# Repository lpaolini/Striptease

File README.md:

# Striptease

Sexy, audio-responsive effects on LED strips.

For [Teensy 4](https://www.pjrc.com/store/teensy40.html) with [Audio Adapter Board](https://www.pjrc.com/store/teensy3_audio.html), by [PJRC](https://www.pjrc.com).

## Quick demo

Shooting video of LEDs is very tricky. Getting the right exposure, focus and colors is not easy at all.
I did my best, but the live effect from my couch is simply not comparable with what you get on video.
I think the main reason is frame rate. This video has been shot at 60 fps, but the real animation runs at about __170 fps__...

[Effect showcase](https://youtu.be/ZliKL7l32wE) (version 3, April 2021)

# Intro

I **love** lights, especially LED lights.

The main goals of this library are:

- to simplify the development of visual effects to be rendered on LED strips, by providing useful abstractions and helpers
- to provide runtime support for rendering simultaneous effects on multiple strips, controlling the transitions and adjusting parameters in real time

# Credits

This work has been inspired by some very cool projects published on the [Cine-Lights](https://www.youtube.com/channel/UCOG6Bi2kvpDa1c8gHWZI5CQ) YouTube channel.
Some of the effects still keep the same name as originally given by the author, even though they have been reimplemented from scratch and might look very different.

Note: at some point, the author decided to go closed-source, distributing compiled (.hex) files only.

# Hardware

## Teensy

This library is designed around the awesome Teensy 4 Development Board, available as [Teensy 4.0](https://www.pjrc.com/store/teensy40.html) or [Teensy 4.1](https://www.pjrc.com/store/teensy41.html), which has been chosen for a number of reasons:

- It's an extremely capable Arduino-compatible board, running an ARM Cortex-M7 at 600 MHz with a floating point math unit, 64 & 32 bits;
- It can be combined with the [Audio Adapter Board](https://www.pjrc.com/store/teensy3_audio.html) for audio I/O and processing;
- It comes with a large set of libraries including two great ones by Paul Stoffregen (Audio and WS2812Serial), described below;
- It's relatively cheap, compared to what it offers.

## Audio Board

The Audio Adapter Board **rev. D** (specific for Teensy 4.x) provides CD-quality stereo ADC/DAC and hardware processing of audio signals.
An optional microphone can be soldered to the board to provide software-switchable mono microphone input, in addition to stereo line input.

Teensy 4.0 provides five serial ports suitable for non-blocking LED driving, while Teensy 4.1 provides a total of eight.
However, when using the Audio Adapter Board, Serial2 and Serial5 are unavailable, leaving us with three channels for Teensy 4.0 and six for Teensy 4.1.

## Level shifter

Teensy 4 runs at 3.3v and all I/O ports operate exclusively at this voltage, thus a level shifter (74HCT245) is required to reliably drive WS2812B LEDs with 5v signals.

## Main board

I've designed a couple of custom PCBs, available in the *hardware* directory: one for Teensy 4.0, the other one for Teensy 4.1, housing connectors (power, IR receiver and LEDs), the DIL socket for the 74HCT245 IC, and a pair of stripline sockets for the Teensy, plus a few passive components. The Audio Adapter Board is sandwiched between the main board and the Teensy using long-terminal stripline connectors soldered to the Audio Adapter Board.

PCBs have been designed using [EAGLE PCB](https://www.autodesk.com/products/eagle) and fabricated by [JLCPCB](https://jlcpcb.com/).

### Main board connectors - Teensy 4.0 version (3 channels)

- POWER: Power (GND, +5v)
- IR-RECV: IR receiver (GND, Data, +3.3v)
- LED1-4: LEDs (CH1, CH2, CH3, CH3)

Note: CH3 is repeated because there are only three independent outputs

### Main board connectors - Teensy 4.1 version (6 channels)

- POWER: Power (GND, +5v)
- IR-RECV: IR receiver (GND, Data, +3.3v)
- PROGR: Program button
- LED1-4: LEDs (CH1, CH2, CH3, CH4)
- LED5-8: LEDs (CH5, CH6, CH6, CH6)

Note: CH6 is repeated because there are only six independent outputs

## WS2812B LED strips

For my projects I prefer high density WS2812B LED strips (144 LED/m) with semi-transparent diffuser, because they look amazing at short distance.
I'm providing photos of the diffuser on top of a printed page, to give you an idea of the transparency.

### Update rate (FPS)

Strips can be any length and they don't need to be matched.
However, being channels driven in parallel, the global update rate is the update rate of the longest strip.
Update rate can be calculated multiplying the time required for transmitting RGB data for a single WS2812B LED (30us) by the number of the LEDs in the strip.
With 6 channels available, up to 3324 LEDs can be driven at 60fps, or up to 1662 at 120fps.
In my home application (about 800 LEDs), the longest strip has 192 LEDs, which translates to about 170fps.

### Powering LEDs

Please be aware that the power rails on the strips have a non-negligible resistance, which would inevitably cause a voltage drop over distance.
The higher the current, the higher the voltage drop (ohm's law).
Total current is the sum of the current flowing through individual LEDs, which in turn depends on the RGB values.
So, depending on the instantaneous state of the LEDs in the strip, the voltage drop could be enough to cause malfunctioning.
To overcome this problem, you might need to *inject* power also at the end of the strip and, if it's very long, every n LEDs (n to be determined).

Personally, I never had to do this, even when driving 240 LEDs at full brightness, but copper thickness of the power rails might differ from one producer to another.

## Power supply

I suggest using excellent quality power supplies. A faulty one can easily destroy your hardware and can even become a threat for your life!

One of my favorite brands is [Traco Power](https://www.tracopower.com/).

## Connectors

For connecting strips to the controller I use professional [Neutrik](https://www.neutrik.com) speakON connectors: [NL4FX](https://www.neutrik.com/en/product/nl4fx) on the cable and [NL4MP](https://www.neutrik.com/en/product/nl4mp) on the controller.

They are rugged, super reliable connectors designed for connecting audio amplifiers to speakers, but they work amazingly well for this purpose too. Current rating is 40A (continuous) and they have four contacts, so one connector can bring power and signals to two strips using a 4-wire cable.

## Infrared receiver

Any common infrared receiver, like TSOP4838 or similar, would be fine.
In my projects I'm using an external one (search for "infrared extender cable"), as they usually come with a convenient red filter which increases the sensitivity by removing unwanted wavelengths.

# Software

Code is built around four *awesome* libraries:

- [FastLED](https://github.com/FastLED/FastLED), for driving LED strips
- [WS2812Serial](https://github.com/PaulStoffregen/WS2812Serial), for non-blocking driving of WS28128B LEDs
- [Audio](https://github.com/PaulStoffregen/Audio), for sophisticated real time processing of audio signal
- [IRMP](https://github.com/IRMP-org/IRMP), for decoding IR remote controller codes (basically any spare remote can be adapted)

## Architecture

Code has been crafted carefully, splitting responsibilites across a number of classes and introducing several useful abstractions.

Teensy 4 is an extremely powerful platform, providing plenty of RAM, flash, CPU and hardware-accelerated floating point math.
For this reason, this library uses floating point math whenever it makes sense, trading unnecessary optimization for code integrity and readibility.

All the effects provided by the library (40+) are self-contained (all state is in own private class members), don't depend on strip length (they adapt to strip length or use normalized addressing) and don't depend on main loop frequency (they rely on timers so that animation speed doesn't depend on global update rate).

# API

## `Strip`

*Strip* is the abstract class for strip implementations (below), providing convenience methods for absolute (integer, 0 to pixel count - 1) or normalized (double, 0 to 1) LED addressing. It makes it easier to manipulate strips in a length-agnostic way.

### `PhysicalStrip<uint16_t SIZE, uint8_t PIN, uint16_t DENSITY>()`

*PhysicalStrip* wraps a FastLED CRGBSet, i.e. a physical strip connected to a pin on the Teensy board.

### `ReversedStrip (Strip *strip)`

*ReversedStrip* wraps an instance of *Strip* for reversing its pixel order.

Example

    Strip A = PhysicalStrip(...) => [1, 2, 3]
    Strip B = ReversedStrip(A)   => [3, 2, 1]

### `JoinedStrip (Strip *strip, Strip *strip2, int16_t gap = 0)`

*JoinedStrip* wraps two instances of *Strip* into a single virtual strip, with an optional gap, i.e. the number of missing LEDs between the two strips.

Example 1 - join two left-to-right strips into a single left-to-right strip

    Strip A = PhysicalStrip(...) => [A1, A2, A3, A4]
    Strip B = PhysicalStrip(...) => [B1, B2, B4, B4, B5, B6]
    Strip C = JoinedStrip(A, B)  => [A1, A2, A3, A4, B1, B2, B3, B4, B5, B6]

Example 2 - join one right-to-left strip with a left-to-right one into a single left-to-right strip

    Strip A = PhysicalStrip(...) => [A5, A4, A3, A2, A1] // right-to-left
    Strip B = PhysicalStrip(...) => [B1, B2, B3, B4, B5] // left-to-right
    Strip C = ReversedStrip(A)   => [A1, A2, A3, A4, A5] 
    Strip D = JoinedStrip(C, B)  => [A1, A2, A3, A4, A5, B1, B2, B3, B4, B5]

### `SubStrip (Strip *strip, int16_t start, int16_t end)`

*SubStrip* wraps an instance of *Strip* for addressing a subsection.

Example 1

    Strip A = PhysicalStrip(...) => [A1, A2, A3, A4, A5, A6]
    Strip B = SubStrip(A, 2, 4) => [A3, A4, A5]

Example 2

    Strip A = PhysicalStrip(...) => [A1, A2, A3, A4]
    Strip B = PhysicalStrip(...) => [B1, B2, B4, B4, B5, B6]
    Strip C = JoinedStrip(A, B)  => [A1, A2, A3, A4, B1, B2, B3, B4, B5, B6]
    Strip D = SubStrip(C, 2, 6) => [A3, A4, B1, B2, B3]

### `Strip overlaying`

All *Strip* implementations expose an *overlay(double opacity)* method which returns an instance of BufferedStrip wrapping the underlying strip.

This is extremely useful for rendering multiple overlayed effects on the same physical LEDs, while keeping them completely isolated from each other.
Each effect will be rendered in its own layer and won't interact with any other effect.

## `Fx`

*Fx* is the abstract class you'll need to extend for implementing your own effects (see *Implementing your effects*).

It defines two abstract methods to be implemented by any effect:

- **void reset()**, called when the effect is selected or reset;
- **void loop()**, called by the main loop when the effect is selected.

See [provided effects](src/fx) for examples.

## `Stage`

*Stage* is the abstract class you'll need to extend for defining your setup (see *Implementing your stage*).
It provides methods for adding strips and effects to your stage.
It is also the right place for calling native FastLED methods for setting color correction and maximum allowed power, to comply with your power supply limits.

Do not call *FastLED.setBrightness()* as global brightness is handled by the *Brightness* class.

## `Multiplex`

*Multiplex* is a virtual effect (it implements the *Fx* interface) which combines up to 20 effects to be rendered concurrently.

## `Controller`

*Controller* exposes high-level actions for the remotes to invoke (e.g. *play*, *pause*, *stop*, *increaseBrightness*, etc.).
It takes care of displaying the selected effect, cycling effects in manual or timed mode, loading and storing effect speed from non-volatile memory and for temporarily displaying systems effects (e.g. for setting input level, cycle speed, effect speed, etc.)

`void setLineInput(uint8_t level)`

Select the stereo line input and setting the input level (0 to 15).
This is the method to be called in your main.cpp for selecting the line input at start.

`void setMicInput(uint8_t gain)`

Select the mono mic input and setting the gain (0 to 63).
This is the method to be called in your main.cpp for selecting the mic input at start.

`void toggleInput()`

Enter input sensitivity setting mode.
If already in input sensitivity setting mode, toggle stereo line input / mono microphone input.

When in input sensitivity setting, a virtual slider fx replaces the currently selected fx for providing a visual indication of:
- current input sensitivity
- current audio signal peak and peak hold
- beat detected (peak hold indicator turn cyan)
- clipping detected (peak hold indicator turns red)

`void increaseInputSensitivity()`

Enter input sensitivity setting mode.
If already in input sensitivity setting mode, increase the sensitivity for the active input.

`void decreaseInputSensitivity()`

Enter input sensitivity setting mode.
If already in input sensitivity setting mode, decrease the sensitivity for the active input.

`void reset()`

Reset current effect.

`void increaseBrightness()`

Increase global brightness.

`void decreaseBrightness()`

Decrease global brightness.

`void setParam(uint8_t value)`

Set a numeric value for the current parameter (can be effect number, input sensitivity, etc., depending on current context).

`void increaseParam()`

Increase the current parameter (can be effect number, input sensitivity, etc., depending on current context).

`void decreaseParam()`

Decrease the current parameter (can be effect number, input sensitivity, etc., depending on current context).

`void selectFx(uint8_t fx)`

Select fx by index number.

`void selectPreviousFx()`

Select previous fx.

`void selectNextFx()`

Select next fx.

`void selectRandomFx()`

Select a random fx.

`void play()`

Enter timed play mode (either sequential or shuffle, based on last selection).

`void sequential()`

Enter timed/sequential play mode.

`void shuffle()`

Enter timer/shuffle play mode.

`void pause()`

Enter manual play mode.

`void playPause()`

Toggle timed/manual play mode.

`void stop()`

Fade out all strips and enter stop mode.

`void cycleSpeed()`

Enter cycle speed setting mode.

A virtual slider fx replaces the currently selected fx for providing a visual indication of the current value.

In this mode setParam(0..10), increaseParam() and decreaseParam() can be used to change the value.

`void setCycleSpeed(uint8_t speed)`

Enter cycle speed setting mode and set cycle speed (0..10).

When in cycle speed setting mode, a virtual slider fx replaces the currently selected fx for providing a visual indication of the current value.

`void increaseCycleSpeed()`

Enter cycle speed setting mode and increase cycle speed.

`void decreaseCycleSpeed()`

Enter cycle speed setting mode and decrease cycle speed.

`void fxSpeed()`

Enter fx speed setting mode.

When in fx speed setting mode, a virtual slider fx replaces the currently selected fx for providing a visual indication of the current value.

`void setFxSpeed(uint8_t speed)`

Enter fx speed setting mode and set cycle speed (0..10).

`void increaseFxSpeed()`

Enter fx speed setting mode and increase fx speed.

`void decreaseFxSpeed()`

Enter fx speed setting mode and decrease fx speed.

## `State`

Effects running in parallel on distinct strips are independent instances with no shared data.

*State* keeps shared, read-only state for use by any effect (most common use is for modulating the effect speed).

## `AudioChannel`

*AudioChannel* consumes instantaneous peak, rms and fft readings provided by the Audio library for the three channels (left, right and mono), and exposes them along with derived indicators: peakSmooth, peakHold, signalDetected, beatDetected, clipping.

| Property | Description |
| :------- | :---------- |
| *peak* | the most recent peak value reported by Audio Library (0 to 1) |
| *rms* | the most recent rms value reported by Audio Library (0 to 1) |
| *rmsLow* | the most recent low-pass filtered (250Hz) rms value reported by Audio Library (0 to 1) |
| *fft* | the most recent fft bins reported by Audio Library (0 to 1) |
| *peakSmooth* | follows *peak* when larger, otherwise loses 1% every 10ms (approx) |
| *peakHold* | follows *peak* when larger, otherwise loses 0.1% every 10ms (approx) |
| *signalDetected* | true if a signal of minimum amplitude 0.01 (0 to 1) was detected in the last 10 seconds |
| *beatDetected* | true if a beat is detected |
| *clipping* | true if the signal exceeds 0.99% of maximum value |
| *fftBin[FFT_BINS]* | FFT bins |
| *bands[FFT_BANDS]* | per band data (peak, peakSmooth, peakHold, peakDetected) |
| *dominantBand* | dominant band (i.e. the one with highest energy) |

### Beat detection

Beat detection is implemented by feeding an instance of `PeakDetector` with the RMS values, which represent the energy content of the signal, calculated from a low-pass filtered (250Hz) copy of the original signal.
Input values are stored in a circular buffer, on which moving average and standard deviation are calculated and used for discriminating peaks with sufficient energy from normal signal fluctuations.

## `AudioTrigger`

`AudioChannel` provides a beatDetected property, but it is instantaneous (i.e. recalculated at every loop). This means that if your effect doesn't read that property at every loop (i.e. only under certain conditions, or when a timer has expired) it might miss it.

`AudioTrigger` provides a convenient way for triggering effects based on audio, storing the beatDetected status over multiple loops. After reading the trigger value, it's automatically reset.
Additionally, it can trigger effects randomly, when no signal is detected.
The number of random events per second can be specified independently for when a signal is detected or when it's quiet.

## `Remote`

`Remote` is the abstract class you'll need to extend for supporting your infrared remote.
Basically, its purpose is to match remote keypresses with `Controller` high-level actions.

In the provided examples I'm using a Sony RM-D420, but more or less any spare remote can be used.

For adding your remote you'll need to:
- flash the [IRMP AllProtocols](https://github.com/IRMP-org/IRMP/tree/master/examples/AllProtocols) example (be sure to change input pin to 22)
- take note of the code detected for each keypress on the remote
- extend the provided [Remote](src/remote/Remote.h) class with your implementation (e.g. MyRemote.h), matching `Controller` actions with remote keys.

See [SonyRemote_RMD420.h](src/remote/SonyRemote_RMD420.h) as a reference.

### Important

- *Remote* implementation, because of some some limitation of the IRMP library, **must be self-contained in the .h file** (it cannot be split in .h/.cpp files).
- Add the relevant **#define** for enabling the your remote's IR protocol (see IRMP documentation) **before importing the library**, i.e. at the top of main.cpp.

## `Brightness`

*Brightness* controls... global brightness.
It also takes care of rendering quick flashes for providing a visual feedback of buttons pressed on the remote control.

## `HarmonicMotion`

The foundation for the majority of the effects implemented so far is the *HarmonicMotion* class, which implements physics for the [harmonic motion](https://en.wikipedia.org/wiki/Simple_harmonic_motion). It emulates the behavior of an object linked with a spring and a damper to a fixed point, with given initial position, fixed point position, velocity, acceleration, elastic constant of the spring, damping, lower and upper bounds with rebound coefficients.
External acceleration (e.g. gravity) is also supported.

Additionally, it provides methods for setting critical damping (no oscillations) or detecting when the system has reached a reasonably stable state (i.e. not moving anymore because all energy has been dissipated or because it's locked in a boundary position).

For simplicity the harmonic motion equation is normalized in respect to the mass, which is always considered equal to 1.

With proper settings of parameters, a large spectrum of behaviors can be represented.
Here is a short list of some common ones:
- infinite oscillation (elastic constant > 0, damping = 0, position != fixed-point position and/or velocity != 0)
- damped oscillation (elastic constant > 0, damping > 0, position != fixed-point position and/or velocity != 0)
- critical damping (elastic constant > 0, damping = critical, position != fixed-point position and/or velocity != 0)
- constant speed (elastic constant = 0, damping = 0, acceleration = 0, velocity != 0)
- constant acceleration (elastic constant = 0, damping = 0, acceleration != 0)
- speed-limited acceleration (elastic constant = 0, damping > 0, acceleration != 0)

Acceleration can be set up to the third order, using 1, 2 or 3 coefficients:
- a1: first order acceleration (constant)
- a2: second order acceleration (acceleration of a1)
- a3: third order acceleration (acceleration of a2)

The object can be rendered in different ways, which can be combined. It can:
- be *mirrored*:, for rendering twin objects symmetrical in respect to the fixed point;
- be *filled*, for filling with color the segment between the object and the fixed point (or between the two objects, if mirrored);
- have a *range*, for rendering the object (or the two objects, if mirrored) as a segment with given starting and ending offset (e.g. a range -2 to 5 renders a segment starting 2 pixels before the nominal position and ending 5 pixels after).

Lower and upper bounds can be set with the respective rebound coefficients (r), for instantaneously changing the speed by multiplying it by the rebound factor:
- r < -1: instantaneous rebound with speed increase
- r = -1: instantaneous perfect rebound
- -1 > r > 0: instantaneous rebound with speed decrease
- r = 0: instantaneous stop (default)
- 0 > r > 1: instantaneous speed decrease (useless)
- r = 1: no bound (no speed change)
- r > 1: instantaneous speed increase (useless)

When setting bounds, a third parameter (`ReboundMode`) can be specified for specifying the boundary of the object to be used as a trigger:
- DEFAULT: the nominal position (default)
- INSIDE: the outer edge of the segment (for triggering when the segment is completely within the bound)
- OUTSIDE: the inner edge of the segment (for triggering when the segment is completely past the bound)

Some very weird behavior can be obtained by using values not possible in the real world, like negative elastic constant, negative damping, or rebound coefficients whose absolute value is greater than one.

Please note all parameters can be changed during the animation (in the *loop* method) for implementing discontinuities or any kind of non-standard behavior.

Most effects use arrays of *HarmonicMotion* instances. A single Teensy 4 can animate a huge number of them at the same time, for very complex animations.

`HarmonicMotion& setup(Strip *strip)`

Initialize an HarmonicMotion instance with a Strip pointer.

`HarmonicMotion& reset()`

Reset all parameters to default value.

`HarmonicMotion& setColor(CRGB color = CRGB::White)`

Set color of the object.

`HarmonicMotion& setAcceleration(double a0, double a1 = 0, double a2 = 0)`

Set acceleration, by providing a0 and optional higher order acceleration constants.

`HarmonicMotion& setElasticConstant(double k)`

Set elastic constant of the spring.

`HarmonicMotion& setDamping(double b)`

Set damping.

`HarmonicMotion& setCriticalDamping()`

Set damping to critical damping value (2 * sqrt(k)).

`HarmonicMotion& setFixedPointPosition(double x0)`

Set fixed point position.

`HarmonicMotion& setFixedPointRandomPosition()`

Set fixed point position randomly.

`HarmonicMotion& setPosition(double x)`

Set position of the object.

`HarmonicMotion& setRandomPosition()`

Set position of the object randomly.

`HarmonicMotion& setVelocity(double v)`

Set velocity of the object.

`HarmonicMotion& setUpperBound(double x, double r = 0, ReboundMode reboundMode = DEFAULT)`

Set upper bound, with optional rebound and bound trigger.

Rebound mode only makes sense when a range is used (i.e. a segment is rendered vs a single pixel).
Its value determines when the bound is triggered:
- DEFAULT: bound is triggered when the nominal position reaches the bound (default)
- INSIDE: bound is triggered when the ending position of the range reaches the bound (i.e. the segment is **within** the bound)
- OUTSIDE: bound is triggered when the starting position of the range reaches the bound (i.e. the segment is **past** the bound)

`HarmonicMotion& setLowerBound(double x, double r = 0, ReboundMode reboundMode = DEFAULT)`

Set lower bound, with optional rebound and bound trigger.

Rebound mode only makes sense when a range is used (i.e. a segment is rendered vs a single pixel).
Its value determines when the bound is triggered:
- DEFAULT: bound is triggered when the nominal position reaches the bound (default)
- INSIDE: bound is triggered when the ending position of the range reaches the bound (i.e. the segment is **within** the bound)
- OUTSIDE: bound is triggered when the starting position of the range reaches the bound (i.e. the segment is **past** the bound)

`HarmonicMotion& setRange(int start, int end)`

Set the starting and ending offset of the segment to be rendered (instead of a single point), in respect to the nominal position.

`HarmonicMotion& setMirror(bool mirror)`

Set mirrored mode (twin objects symmetrical to the fixed point).

`HarmonicMotion& setFill(bool fill)`

Set fill mode (fill the segment between the object nominae position and the fixed point position with color.

`HarmonicMotion& setShowWhenStable(bool showWhenStable)`

Show or hide the object when its position is stable.

`HarmonicMotion& setOverwrite(bool overwrite)`

Add or overwrite existing color data.

`double getFixedPointPosition()`

Get current fixed point position.

`double getPosition()`

Get current object position.

`double getVelocity()`

Get current object velocity.

`bool isStable()`

Detect if position is stable (not moving anymore).
Position is considered to be stable when one of the following conditions become true:
- both the overall acceleration and velocity are negligible
- the overall acceleration is negative, the object is at the lower bound and velocity is negligible
- the overall acceleration is positive, the object is at the upper bound and velocity is negligible

`void loop()`

Main loop.

### Method chaining

All setters return the current instance, for easy chaining of methods.

The following example would animate a 6-pixel red segment starting at position 0 with random speed between 100 and 200 pixel/s, rebounding past the upper bound and stopping within the lower bound.

    item.reset()
        .setColor(CRGB::Red)
        .setPosition(0)
        .setVelocity(random8(100, 200))
        .setLowerBound(strip->first(), 0, INSIDE)
        .setUpperBound(strip->last(), -1, OUTSIDE)
        .setRange(0, 5);

# Implementing new effects

You can easily create new effects by extending the *Fx* class.

My suggestion is to look at the provided effects, as they are self contained, quite compact in size, and relatively easy to understand.

# Implementing your stage

You can easily implement your own stage by extending the *Stage* class.

Two fully functional examples are provided as external repositories:

- [https://github.com/lpaolini/Striptease-example-Teensy4.0](https://github.com/lpaolini/Striptease-example-Teensy4.0)
- [https://github.com/lpaolini/Striptease-example-Teensy4.1](https://github.com/lpaolini/Striptease-example-Teensy4.1)

# Feedback

Please be free to [contact me](mailto:lookap@gmail.com), open issues and submit PRs.

Happy Stripteasing! :-)

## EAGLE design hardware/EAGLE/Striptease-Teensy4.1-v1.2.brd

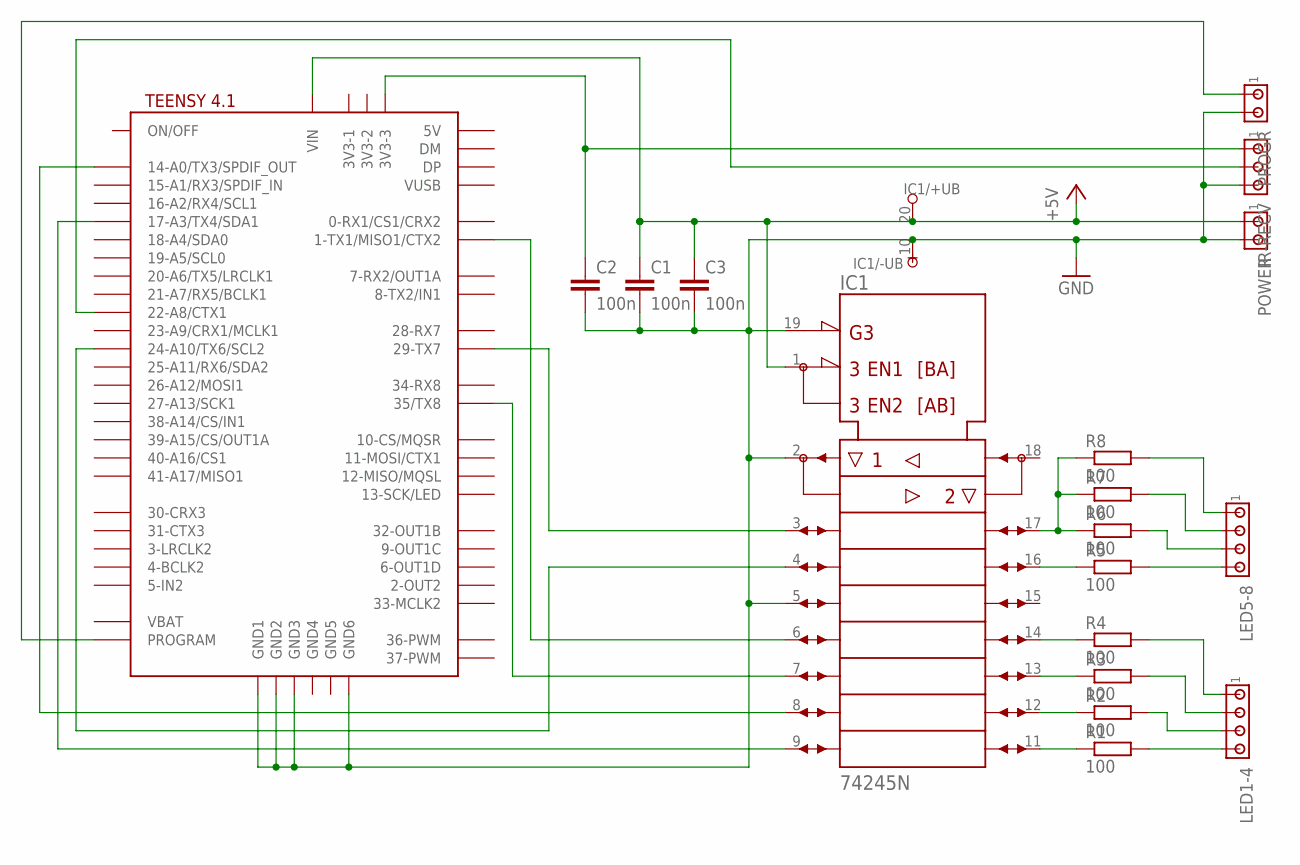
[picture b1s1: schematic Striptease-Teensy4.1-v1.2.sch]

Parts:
C1, C2, C3: 100n; C050-025X075
IC1: 74245N; DIL20
IR-RECV: MTA03-100; 10X03MTA
LED1-4, LED5-8: MTA04-100; 10X04MTA
POWER: MTA02-100; 10X02MTA
PROGR: MTA02-100; 10X02MTA
R1, R2, R3, R4, R5, R6, R7, R8: 100; 0207/10
U$3: TEENSY41-E; TENNSY41-E

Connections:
+5V: C1.1, C3.1, IC1.1 (DIR), IC1.20 (+UB), POWER.1, U$3.VIN
GND: C1.2, C2.2, C3.2, IC1.2 (A1), IC1.5 (A4), IC1.10 (-UB), IC1.19 (!G), IR-RECV.3, POWER.2, PROGR.2, U$3.GND1, U$3.GND2, U$3.GND3, U$3.GND6
unnamed: C2.1, IR-RECV.1, U$3.3V3-3
unnamed: PROGR.1, U$3.PROGRAM
unnamed: IC1.16 (B3), R5.1
unnamed: LED5-8.2, R7.2
unnamed: LED1-4.2, R3.2
unnamed: LED1-4.3, R2.2
unnamed: LED1-4.4, R1.2
unnamed: LED5-8.1, R8.2
unnamed: IC1.11 (B8), R1.1
unnamed: IC1.12 (B7), R2.1
unnamed: IC1.13 (B6), R3.1
unnamed: IC1.17 (B2), R6.1, R7.1, R8.1
unnamed: IC1.14 (B5), R4.1
unnamed: LED1-4.1, R4.2
unnamed: LED5-8.4, R5.2
unnamed: LED5-8.3, R6.2
unnamed: IC1.9 (A8), U$3.17-A3/TX4/SDA1
unnamed: IC1.8 (A7), U$3.14-A0/TX3/SPDIF_OUT
unnamed: IC1.7 (A6), U$3.35-TX8 (35/TX8)
unnamed: IC1.6 (A5), U$3.1-TX1/MISO1/CTX2
unnamed: IC1.4 (A3), U$3.24-A10/TX6/SCL2
unnamed: IC1.3 (A2), U$3.29-TX7
unnamed: IR-RECV.2, U$3.22-A8/CTX1

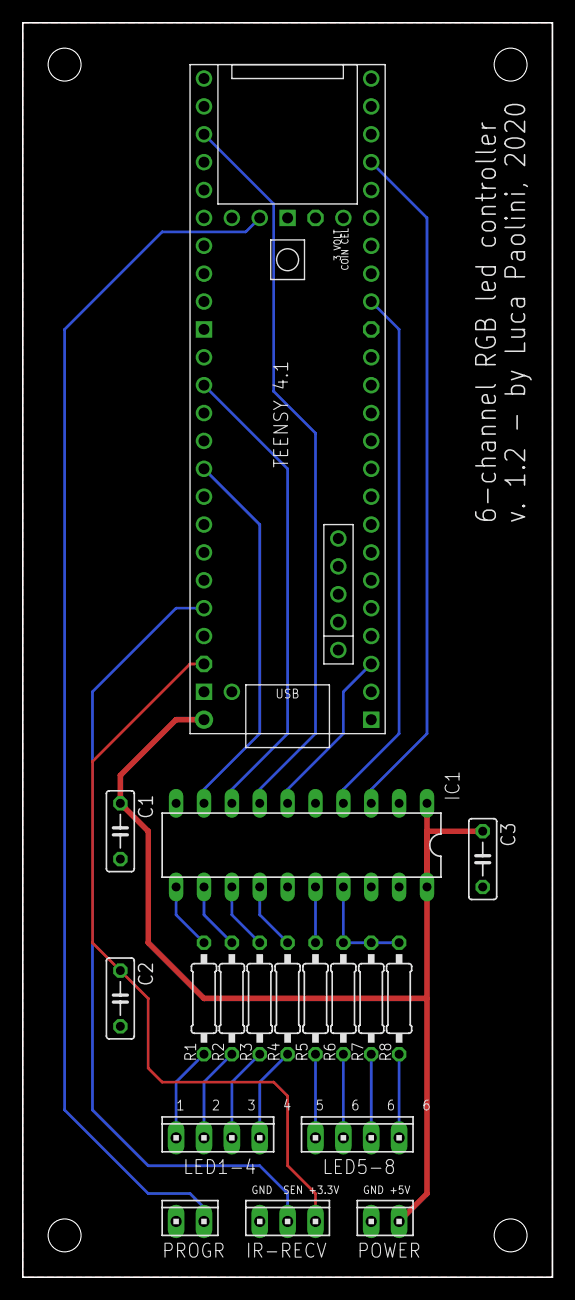
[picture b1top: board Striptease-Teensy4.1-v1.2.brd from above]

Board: 2 copper layers, 48.3 x 114.3 mm, 18 parts (0 on the bottom side), 25 nets.

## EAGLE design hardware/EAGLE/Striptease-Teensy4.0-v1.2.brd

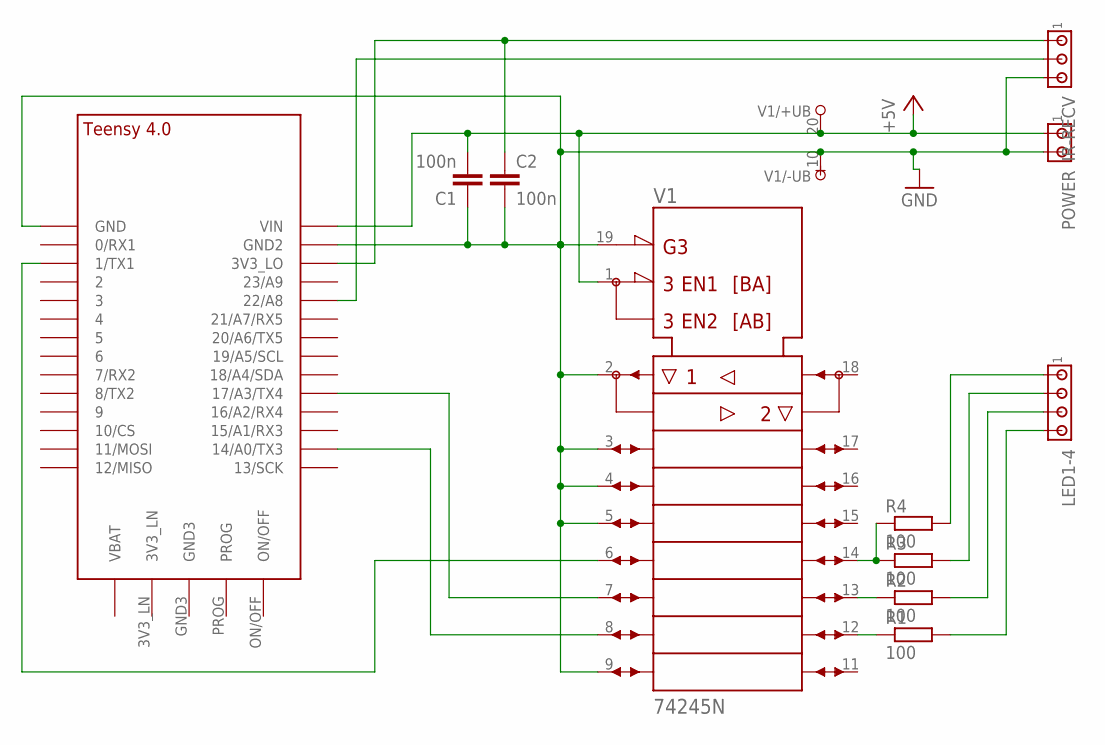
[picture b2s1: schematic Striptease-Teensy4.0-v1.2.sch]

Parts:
C1, C2: 100n; C050-025X075
IR-RECV: MTA03-100; 10X03MTA
LED1-4: MTA04-100; 10X04MTA
POWER: MTA02-100; 10X02MTA
R1, R2, R3, R4: 100; 0207/10
U$1: TEENSY_4.0-BASIC
V1: 74245N; DIL20

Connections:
+5V: C1.2, POWER.1, U$1.VIN, V1.1 (DIR), V1.20 (+UB)
GND: C1.1, C2.2, IR-RECV.3, POWER.2, U$1.GND, U$1.GND2, V1.2 (A1), V1.3 (A2), V1.4 (A3), V1.5 (A4), V1.9 (A8), V1.10 (-UB), V1.19 (!G)
unnamed: IR-RECV.2, U$1.22/A8
unnamed: C2.1, IR-RECV.1, U$1.3V3_LO
unnamed: LED1-4.1, R4.2
unnamed: LED1-4.2, R3.2
unnamed: LED1-4.3, R2.2
unnamed: LED1-4.4, R1.2
unnamed: U$1.14/A0 (14/A0/TX3), V1.8 (A7)
unnamed: R1.1, V1.12 (B7)
unnamed: R2.1, V1.13 (B6)
unnamed: R3.1, R4.1, V1.14 (B5)
unnamed: U$1.17/A3 (17/A3/TX4), V1.7 (A6)
unnamed: U$1.1/TX (1/TX1), V1.6 (A5)

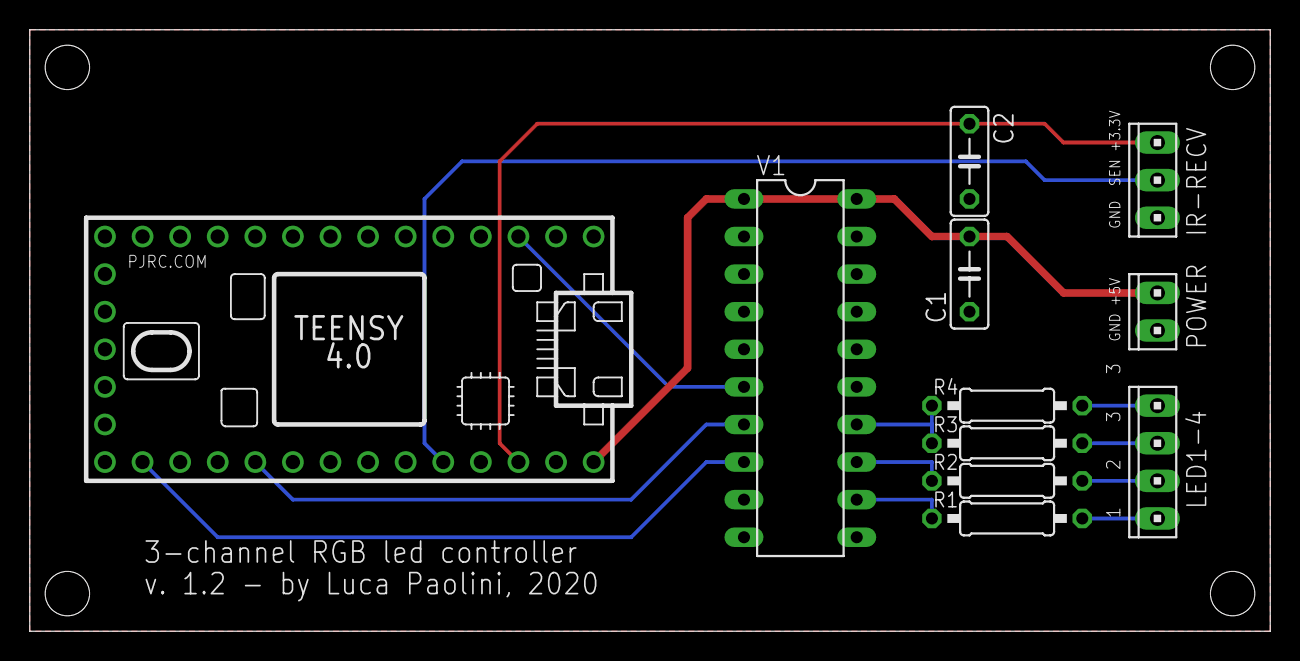
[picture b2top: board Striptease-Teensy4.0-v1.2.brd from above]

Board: 2 copper layers, 83.8 x 40.6 mm, 11 parts (0 on the bottom side), 14 nets.

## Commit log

2021-01-09 Initial commit.
2021-01-09 Fixed name.
2021-01-09 Removed teensy libs.
2021-01-09 Fixed library.json description.
2021-01-09 Added README.
2021-01-09 Added hardware.
2021-01-11 Implement in and out for Strip shiftUp/shiftDown.
2021-01-11 Add images of rail and diffuser.
2021-01-11 Add default 'in' value for Strip shiftUp/shiftDown.
2021-01-11 Simplify code.
2021-01-11 Rebuild Photos fx using HarmonicMotion.
2021-01-11 Improve and extend Strip functionality.
2021-01-11 Make Strip abstract, implement PhysicalStrip.
2021-01-11 Implement ReversedStrip.
2021-01-11 Fix imports.
2021-01-11 Implement JoinedStrip.
2021-01-11 Implement JoinedStrip distance.
2021-01-11 Cleanup.
2021-01-11 Update documentation.
2021-01-11 Fix changelog.
2021-01-11 Updated documentation.
2021-01-12 Bugfix: bypass JoinedStrip buffer if distance = 0.
2021-01-12 Allow selection of effect to enter play mode.
2021-01-12 Rename Controller mode NORMAL to PLAY.
2021-01-16 Implement DeepSpace effect direction changes.
2021-01-16 Add email address to README.
2021-01-20 Improve DeepSpace effect.
2021-01-20 Add SerialRemote reset command.
2021-01-20 Minor fixes.
2021-01-22 Adjust audio memory blocks.
2021-01-22 Implement trigger.
2021-01-22 Refactor and cleanup.
2021-01-22 Make Juggle fx speed adjustable.
2021-01-22 Update changelog.
2021-01-22 Fix examples.
2021-01-22 Update library.json version.
2021-01-24 Fix circuit for Teensy 4.1.
2021-01-25 Improve and refactor Fire fx.
2021-01-25 Fix Matrix fx sound reactivity.
2021-02-02 Add utility methods for setting initial audio input.
2021-02-02 Replace custom palette with predefined.
2021-02-04 Fix minimum param for DeepSpace fx.
2021-02-04 Allow trigger to detect beat over an interval.
2021-02-04 Improve Fire fx audio responsiveness.
2021-02-04 Add explicit dependency on WS2812Serial lib.
2021-02-06 Reduce minimum brightness.
2021-02-06 Add ColorBar fx.
2021-02-06 Fix DeepSpace fx freeze bug.
2021-02-06 Update SpeedMeter background color.
2021-02-06 Update IRMP library to version 3.4.0.
2021-02-06 Bumped version to 1.1.4.
2021-02-06 Update examples.
2021-02-06 Fix number of FFT bins.
2021-02-06 Implement low-frequency-only beat detection.
2021-02-06 Fix warning message.
2021-02-07 Add low-frequency-only beat detection for mono channel.
2021-02-09 Replace AudioChannel trigger with AudioTrigger.
2021-02-09 Reimplement Strip implementations.
2021-02-09 Implement SubStrip.
2021-02-09 Bump version to 1.2.0.
2021-02-09 Update README.
2021-02-09 Add FFT for mono channel.
2021-02-09 Increase AudioMemory blocks.
2021-02-09 Implement audio memory and cpu monitoring.
2021-02-09 Improve system monitoring.
2021-02-09 Fix Timer behavior.
2021-02-10 Fix AudioTrigger.
2021-02-10 Reimplement Matrix.
2021-02-10 Fix paintNormalizedSize method.
2021-02-10 Reduce PeakMeter flashing on beat.
2021-02-10 Implement BufferedStrip.
2021-02-16 Move audioChannel and state to Fx.
2021-02-16 Implement Strip buffering.
2021-02-16 Implement fx VU2.
2021-02-16 Fix dependency version.
2021-02-16 Fix documentation.
2021-02-17 Fixed a few typos and grammatical errors
2021-02-18 Change visibility of isInRange and limitToRange.
2021-02-18 Bump version to 1.2.1
2021-02-18 Bugfixes.
2021-02-19 Fix HarmonicMotion bug caused by wrong assignment.
2021-02-19 Add HarmonicMotion methods for random positioning.
2021-02-19 Refactor Multiplex, extending the limit to 9 fx.
2021-02-19 Implement JoinedStrip missing corner case.
2021-02-19 Sanitize sensitive arguments and fix corner cases.
2021-02-19 Cleanup Ants fx.
2021-02-19 Implement Bounce fx.
2021-02-19 Bump version to 1.2.2
2021-02-20 Change connector names in EAGLE boards.
2021-02-20 Add connector pinout for LEDs in EAGLE boards.
2021-02-20 Bump version to 1.2.3.
2021-02-22 Adopt 'Keep a Changelog'.
2021-02-23 Replace Strip sanitize with crop.
2021-02-23 Fix Fx flush.
2021-02-23 Bump version to 1.2.5.
2021-02-23 Move Strip implementation into strip directory.
2021-02-23 Refactoring.
2021-02-25 Improve FFT.
2021-02-25 Use fft for Scroller fx.
2021-02-25 Use fftBands for Spectrum fx.
2021-02-25 Implement EllipticMotion.
2021-02-25 Add Spiral fx (EllipticMotion demo).
2021-02-25 Bump version to 1.2.6.
2021-02-26 Allow addFx up to 9 effects.
2021-02-26 Refactor examples.
2021-02-26 Add explicit dependency on WS2812Serial.
2021-02-26 Add custom color support to VU2 fx.
2021-02-26 Force BlackOut effect to clear at each loop.
2021-02-26 Add credit info.
2021-02-28 Implement Scroller choking.
2021-02-28 Disable VU2 when stable.
2021-02-28 Fix wrong index.
2021-03-02 Implement peak detector per band.
2021-03-02 Drop double rotating hue.
2021-03-02 Store raw values in bands (vs dB).
2021-03-02 Make Spectrum independent from strip length.
2021-03-19 Implement configurable stats and standby timers.
2021-03-19 Add explicit dependency on Audio library.
2021-03-19 Add SerialRemote commands for brightness control.
2021-03-19 Bump version to 1.2.8.
2021-03-25 Implement solid color Background effect.
2021-03-25 Implement Ripple parametric background color.
2021-03-25 Reduce Vertigo inhibit time.
2021-03-25 Increase minimum brightness.
2021-03-25 Implement Controller setBrightness method.
2021-03-25 Bump version to 1.2.9.
2021-04-10 Fix Timer.
2021-04-10 Bump version to 1.2.10.
2021-12-03 Improved FXs, added customization options.
2021-12-03 Skipped first EEPROM location.
2021-12-03 Critical bugfix.
    Probable cause of random crashes.
2021-12-03 Added Motion class.
2021-12-03 Fixed examples.
2021-12-03 Bump version to 1.2.11.
2021-12-03 Updated to IRMP v.3.5.1.
2021-12-09 Add HarmonicMotion critical damping correction factor.
2021-12-09 Fix EEPROM persistence of param value.
2021-12-09 Add Interval for easier porting of Pixelblaze fx.
2021-12-09 Add Pixelblaze's RippleReflections fx.
2021-12-09 Add Pixelblaze's RainbowMelt fx.
2021-12-09 Update Elastic fx.
2021-12-09 Bump version to 1.2.12.
2021-12-11 Fix DeepSpace last pixel bug.
2021-12-11 Bump version to 1.2.13.
2021-12-11 Fix RainbowMelt index upper limit.
2021-12-11 Replace float with double.
2021-12-11 Change Interval precision to microseconds.
2021-12-12 Add Easing easeInSite.
2021-12-12 Move Pixelblaze-style functions to Fx.
2021-12-12 Add FastPulse and MarcingRainbow fx.
2022-01-16 Implement audio muting.
2022-01-16 Add missing default return values.
2022-01-16 Implement Strip getIndex and getPosition methods.
2022-01-16 Reimplement State rotatingHue.
2022-01-16 Upgrade FastLED to 3.5.0.
2022-01-16 Add more fx ported from Pixelblaze.
2022-04-18 Updated README.
2022-04-19 Add missing includes.
2022-04-19 Bump version to 1.2.14.
2023-12-25 Fix wrong calculation of pixel range in mirrored mode.
2023-12-25 Update libraries.
2024-12-17 Updated libraries.
2024-12-18 Simplify Strip and subclasses.
2024-12-18 Implement buffered strip opacity.
2024-12-19 Group virtual strips with namespace.
2024-12-19 Rename Strip method buffered() to overlay().
2024-12-22 Use double for Strip index.
    This allows protecting the index from integer rollover.
2024-12-23 Remove HarmonicMotion default color.
    When no color is specified nothing will be rendered.
2024-12-23 Expose HarmonicMotion acceleration.
2024-12-23 Make system effects smoother.
2024-12-24 Implement HarmonicMotion ReboundMode.
2024-12-25 Fix Strip paintRandomPos.
2024-12-28 Add remotes.
2024-12-28 Adapt existing effects.
2024-12-28 Add new effects (sparks, traffic).
2024-12-28 Delegate creation of PhysicalStrip to addStrip.
2024-12-28 Changed version to 1.3.0-beta1
2025-01-02 Improve Traffic fx.
2025-01-02 Group remote-related classes.
2025-01-02 Add virtual strips to Stage.h
2025-01-02 Group audio-related classes.
2025-01-02 Remove examples.
2025-01-02 Refactoring: remove unnecessary #includes.
2025-01-03 Add dummy main.cpp.
2025-01-03 Simplify the creation of physical strips.
2025-01-03 Bump version to 1.3.0-beta3.
2025-01-03 Increase the number of multiplexed effects to 20.
2025-01-03 Change overlay opacity to double (range 0 to 1).
2025-01-05 Fix README SubStrip examples.
2025-01-05 Simplify BufferedStrip.
2025-01-05 Upgrade FastLED to v3.9.9.
2025-01-06 Replace Stage fadeOut() with fade(uint8_t amount).
2025-01-06 Implement Stage blur(uint8_t amount).
2025-01-07 Make "add" argument non-optional in all Strip paint mehods.
2025-01-09 Implement Gradient.
2025-01-09 Bumped version to 1.4.0-beta1.
2025-01-09 Fix Gradient.
2025-01-09 Refactoring Strip virtuals.
2025-01-09 Renamed Strip "add" argument to "overlay".
2025-01-09 Refactor Gradient.
2025-01-09 Reimplemented Strip boundaries.
2025-01-11 Implemented Gradient getRandomColor().
2025-01-11 Slightly revised Fireworks effect.
2025-01-11 Slightly revised Jelly effect.
2025-01-11 Implemented Scan effect.
2025-01-11 Implemented Sunset effect.
2025-01-11 Slightly revised Traffic effect.
2025-01-12 Bumped version to 1.4.0.
